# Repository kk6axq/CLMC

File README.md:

# CLMC (Closed Loop Motor Controller)
This is a closed loop brushed DC motor controller project, completed for an honors enrichment contract in EGR101 at Arizona State University. The goal was to develop the hardware and software to enabled PID based control of position, velocity, and acceleration in an encoder equipped motor. So far, the project has met its minimum requirements, however there are several areas to improve. For more background on the project and architectures, see the Wiki.

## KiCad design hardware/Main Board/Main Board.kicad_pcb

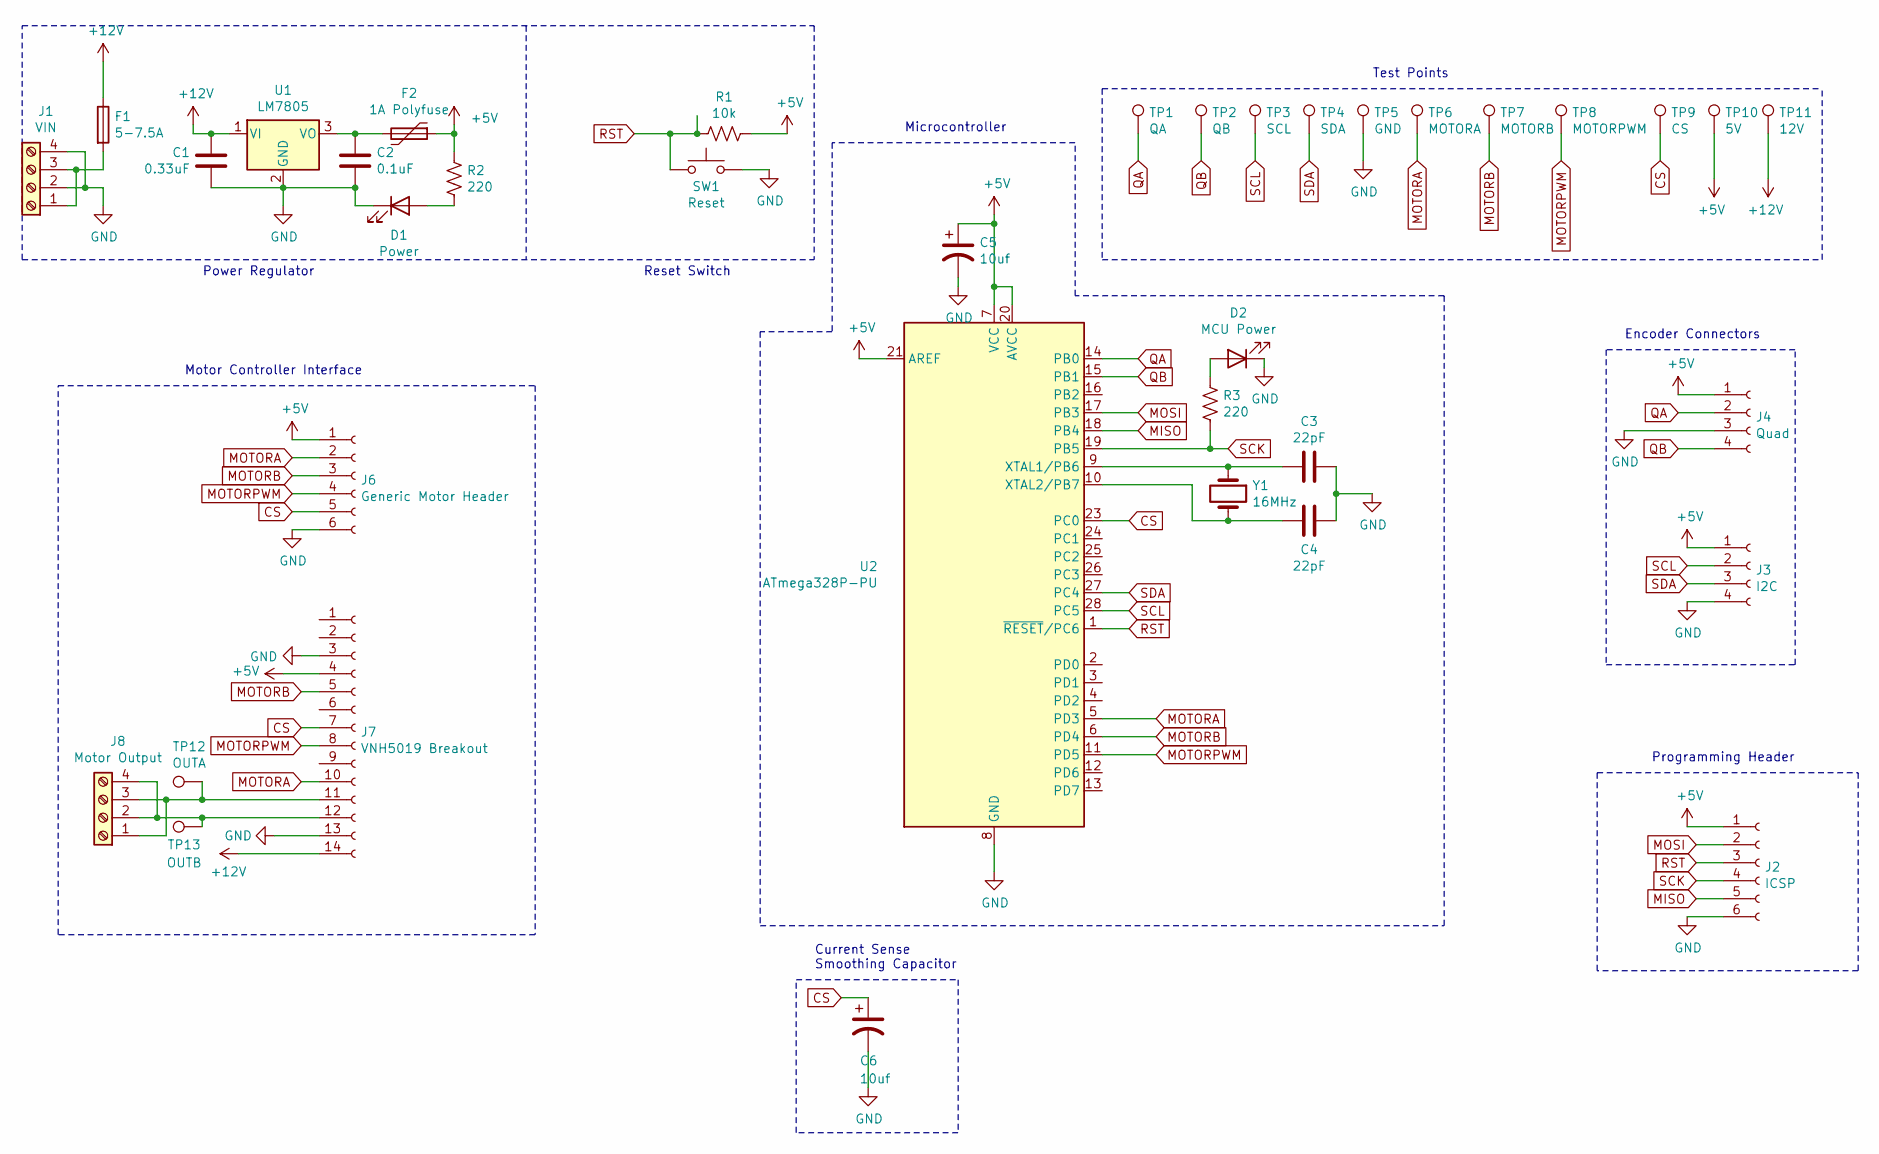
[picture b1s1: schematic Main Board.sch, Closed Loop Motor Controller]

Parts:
C1: 0.33uF; C_1206_3216Metric
C2: 0.1uF; C_1206_3216Metric
C3, C4: 22pF; C_Rect_L4.0mm_W2.5mm_P2.50mm
C5, C6: 10uf; CP_Radial_D5.0mm_P2.00mm
D1: Power; LED_D5.0mm
D2: MCU Power; LED_D5.0mm
F1: 5-7.5A; TerminalBlock_bornier-2_P5.08mm
F2: 1A Polyfuse; C_Rect_L7.2mm_W3.5mm_P5.00mm_FKS2_FKP2_MKS2_MKP2
J1: VIN; 2x2TerminalBlock
J2: ICSP; 6PinEdgeConnector
J3: I2C; 4PinEdgeConnector
J4: Quad; 4PinEdgeConnector
J6: Generic Motor Header; 6PinEdgeConnector
J7: VNH5019 Breakout; VNH5019Footprint
J8: Motor Output; 2x2TerminalBlock
R1: 10k; R_Axial_DIN0204_L3.6mm_D1.6mm_P5.08mm_Vertical
R2, R3: 220; R_Axial_DIN0204_L3.6mm_D1.6mm_P5.08mm_Vertical
SW1: Reset; SW_TH_Tactile_Omron_B3F-10xx
TP1: QA; TestPoint_Pad_D2.0mm
TP2: QB; TestPoint_Pad_D2.0mm
TP3: SCL; TestPoint_Pad_D2.0mm
TP4: SDA; TestPoint_Pad_D2.0mm
TP5: GND; TestPoint_Pad_D2.0mm
TP6: MOTORA; TestPoint_Pad_D2.0mm
TP7: MOTORB; TestPoint_Pad_D2.0mm
TP8: MOTORPWM; TestPoint_Pad_D2.0mm
TP9: CS; TestPoint_Pad_D2.0mm
TP10: 5V; TestPoint_Pad_D2.0mm
TP11: 12V; TestPoint_Pad_D2.0mm
TP12: OUTA; TestPoint_Pad_D2.0mm
TP13: OUTB; TestPoint_Pad_D2.0mm
U1: LM7805; TO-220-3_Horizontal_TabDown
U2: ATmega328P-PU; DIP-28_W7.62mm
Y1: 16MHz; PinHeader_1x02_P2.54mm_Vertical

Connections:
+5V: C5.1, F2.1, J2.1, J3.1, J4.1, J6.1, J7.4, R1.1, R2.1, TP10.1, U2.7 (VCC), U2.20 (AVCC), U2.21 (AREF)
+12V: C1.1, F1.1, J7.14, TP11.1, U1.1 (VI)
CS: C6.1, J6.5, J7.7, TP9.1, U2.23 (PC0)
GND: C1.2, C2.2, C3.1, C4.1, C5.2, C6.2, D1.1 (K), D2.1 (K), J1.2, J1.4, J2.6, J3.4, J4.3, J6.6, J7.3, J7.13, SW1.2, TP5.1, U1.2 (GND), U2.8 (GND), U2.22 (GND)
MISO: J2.5, U2.18 (PB4)
MOSI: J2.2, U2.17 (PB3)
MOTORA: J6.2, J7.10, TP6.1, U2.5 (PD3)
MOTORB: J6.3, J7.5, TP7.1, U2.6 (PD4)
MOTORPWM: J6.4, J7.8, TP8.1, U2.11 (PD5)
unnamed: C2.1, F2.2, U1.3 (VO)
unnamed: C3.2, U2.9 (XTAL1/PB6), Y1.1
unnamed: C4.2, U2.10 (XTAL2/PB7), Y1.2
unnamed: D1.2 (A), R2.2
unnamed: D2.2 (A), R3.1
unnamed: F1.2, J1.1, J1.3
unnamed: J7.11, J8.1, J8.3, TP12.1
unnamed: J7.12, J8.2, J8.4, TP13.1
QA: J4.2, TP1.1, U2.14 (PB0)
QB: J4.4, TP2.1, U2.15 (PB1)
RST: J2.3, R1.2, SW1.1, U2.1 (~RESET~/PC6)
SCK: J2.4, R3.2, U2.19 (PB5)
SCL: J3.2, TP3.1, U2.28 (PC5)
SDA: J3.3, TP4.1, U2.27 (PC4)

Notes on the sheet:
Power Regulator
Test Points
Programming Header
Encoder Connectors
Microcontroller
Reset Switch
Current Sense Smoothing Capacitor
Motor Controller Interface

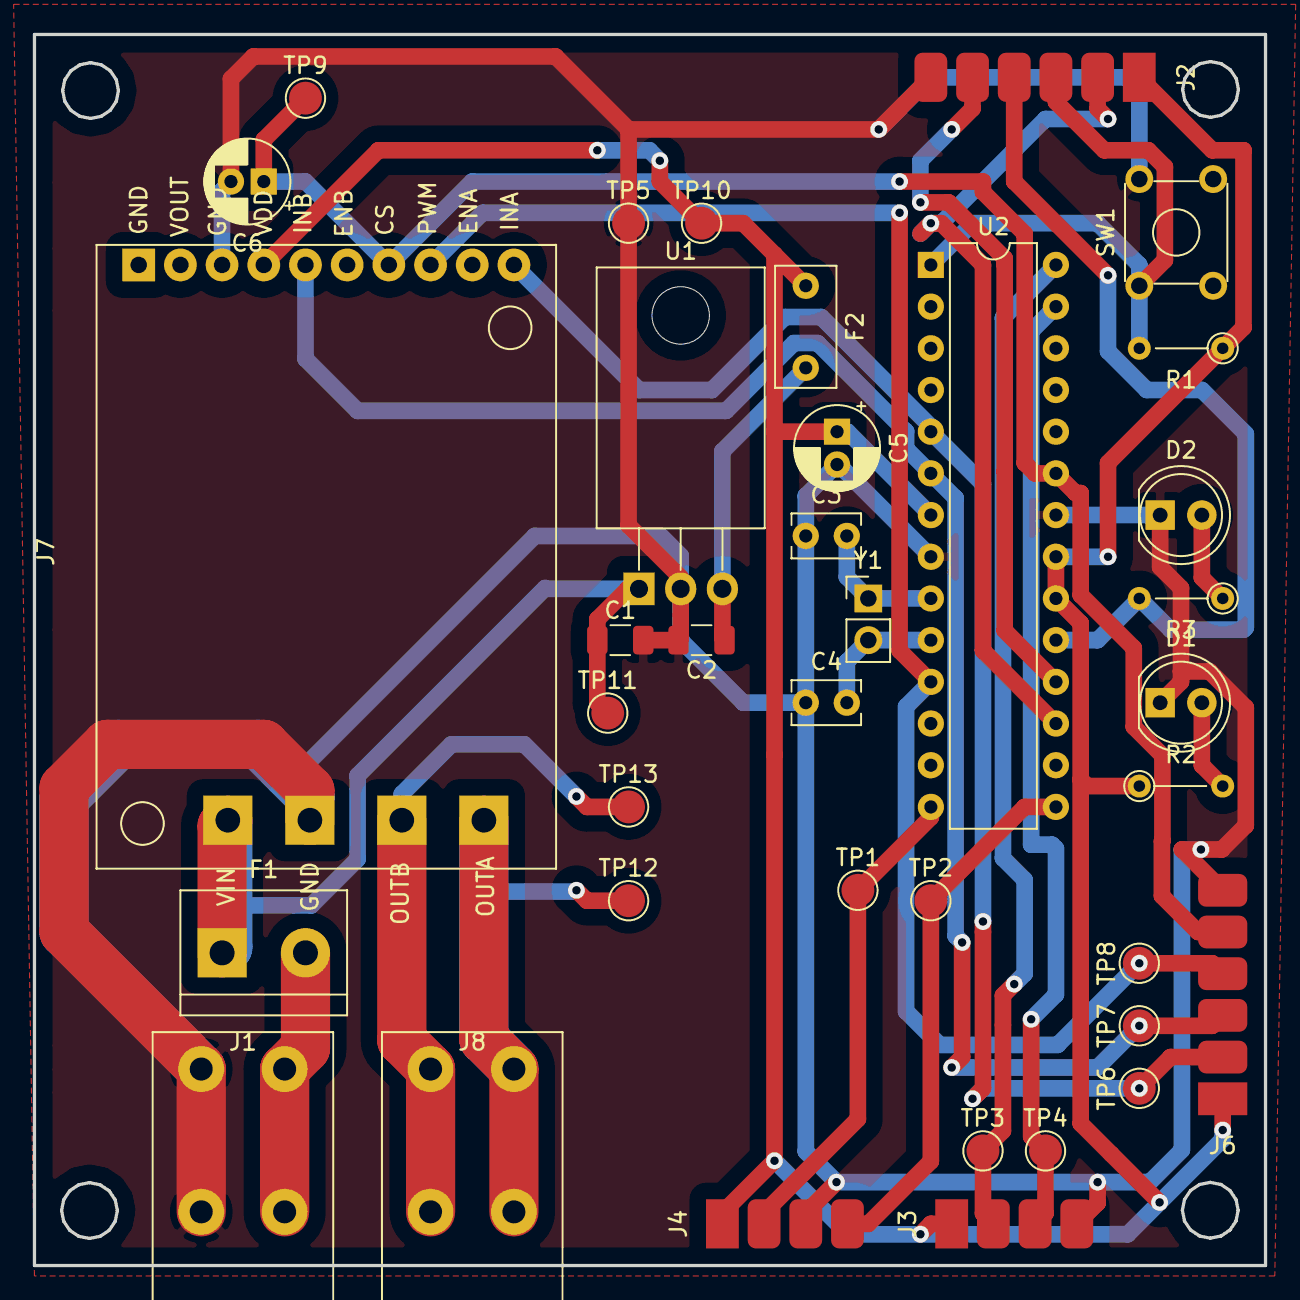
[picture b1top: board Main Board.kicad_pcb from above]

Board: 2 copper layers, 75.0 x 75.0 mm, 37 parts (0 on the bottom side), 23 nets.

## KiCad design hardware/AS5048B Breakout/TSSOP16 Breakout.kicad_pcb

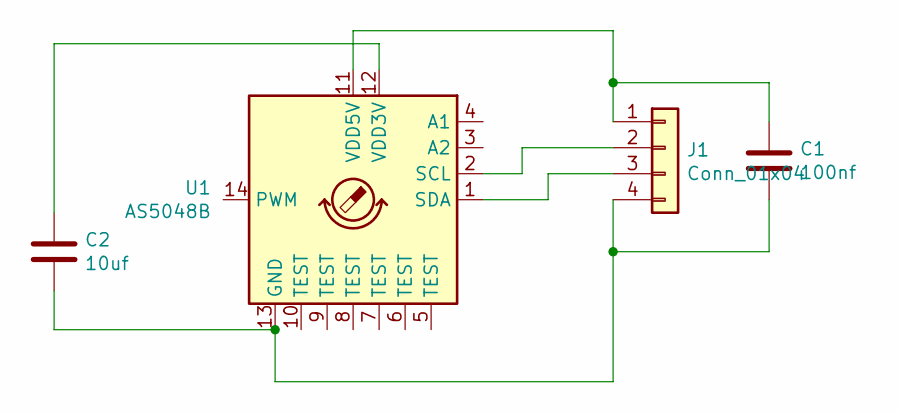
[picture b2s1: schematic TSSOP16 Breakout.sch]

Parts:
C1: 100nf; C_1206_3216Metric_Pad1.42x1.75mm_HandSolder
C2: 10uf; C_1206_3216Metric_Pad1.42x1.75mm_HandSolder
J1: Conn_01x04; PinHeader_1x04_P2.00mm_Vertical
U1: AS5048B; TSSOP-14_4.4x5mm_P0.65mm

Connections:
unnamed: C1.1, J1.1, U1.11 (VDD5V)
unnamed: C1.2, C2.2, J1.4, U1.13 (GND)
unnamed: C2.1, U1.12 (VDD3V)
unnamed: J1.2, U1.2 (SCL)
unnamed: J1.3, U1.1 (SDA)

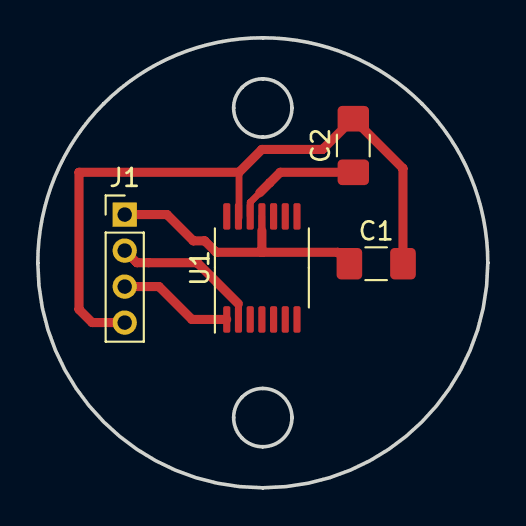
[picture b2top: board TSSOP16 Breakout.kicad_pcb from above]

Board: 2 copper layers, 25.0 x 25.0 mm, 4 parts (0 on the bottom side), 5 nets.

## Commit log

2020-10-12 Add CAD files
2020-10-14 Add enclosure files
2020-10-14 Add photo to readme
2020-10-15 Add HTML Bill of Materials/Part Placer
2020-10-23 Add motor sensor mount
2020-10-28 Add Base Isometric View Photo
2020-11-17 Add several features
    Converted ifdefs to ifs to allow for real time mode switching.
    Added EEPROM config load/save.
    Added help menu.
    Added options for real time tuning.
2020-11-18 Add final changes to implement EEPROM persistence
    Added several new commands, help menu, etc.
    Added EEPROM and EEPROM load on boot.
    Verified EEPROM functionality.
2020-11-18 Add serial timeout function
    Reduces idle time, testing showed it was 8ms, so the timeout is now 20ms. If the byte arrives early, it will read it immediately.
2021-07-17 Add block diagram
